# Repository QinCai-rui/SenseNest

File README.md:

# SenseNest
Smart Sensing for a Healthier Home - Compatible with Home Assistant

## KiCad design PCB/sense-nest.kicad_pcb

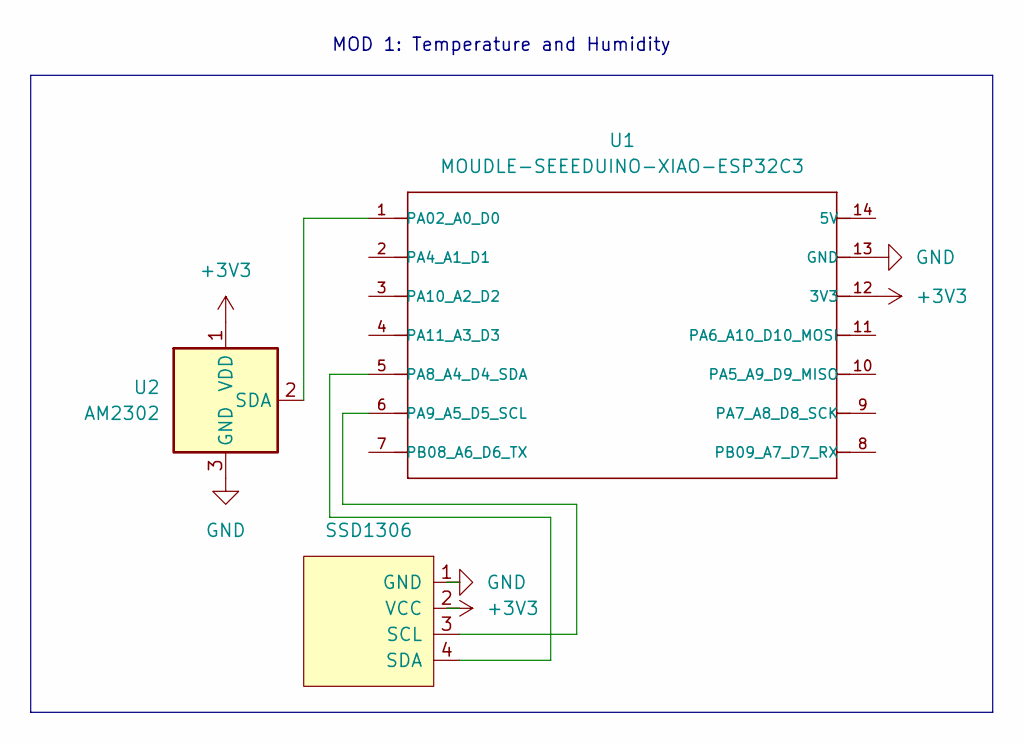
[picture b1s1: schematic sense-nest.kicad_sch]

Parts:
Brd1: SSD1306; 128x64OLED
U1: MOUDLE-SEEEDUINO-XIAO-ESP32C3; MOUDLE14P-SMD-2.54-21X17.8MM
U2: AM2302; ASAIR_AM2302_P2.54mm_Vertical

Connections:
+3V3: Brd1.2 (VCC), U1.12 (3V3), U2.1 (VDD)
GND: Brd1.1 (GND), U1.13 (GND), U2.3 (GND), U2.4 (GND)
unnamed: Brd1.3 (SCL), U1.6 (PA9_A5_D5_SCL)
unnamed: Brd1.4 (SDA), U1.5 (PA8_A4_D4_SDA)
unnamed: U1.1 (PA02_A0_D0), U2.2 (SDA)

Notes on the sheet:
MOD 1: Temperature and Humidity

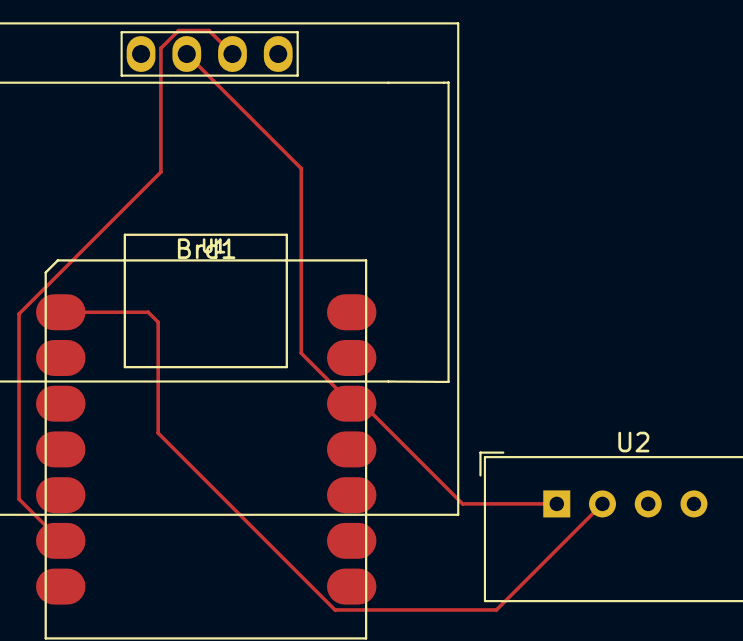
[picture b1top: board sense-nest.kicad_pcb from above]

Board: 2 copper layers, 3 parts (0 on the bottom side), 5 nets.

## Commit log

2025-07-03 add plan document
2025-07-06 add initial PCB
2025-07-06 add gitignore
2025-07-06 initial pcb; libraries
2025-07-06 update gitignore
2025-07-06 rm random file
2025-07-07 update PCB
